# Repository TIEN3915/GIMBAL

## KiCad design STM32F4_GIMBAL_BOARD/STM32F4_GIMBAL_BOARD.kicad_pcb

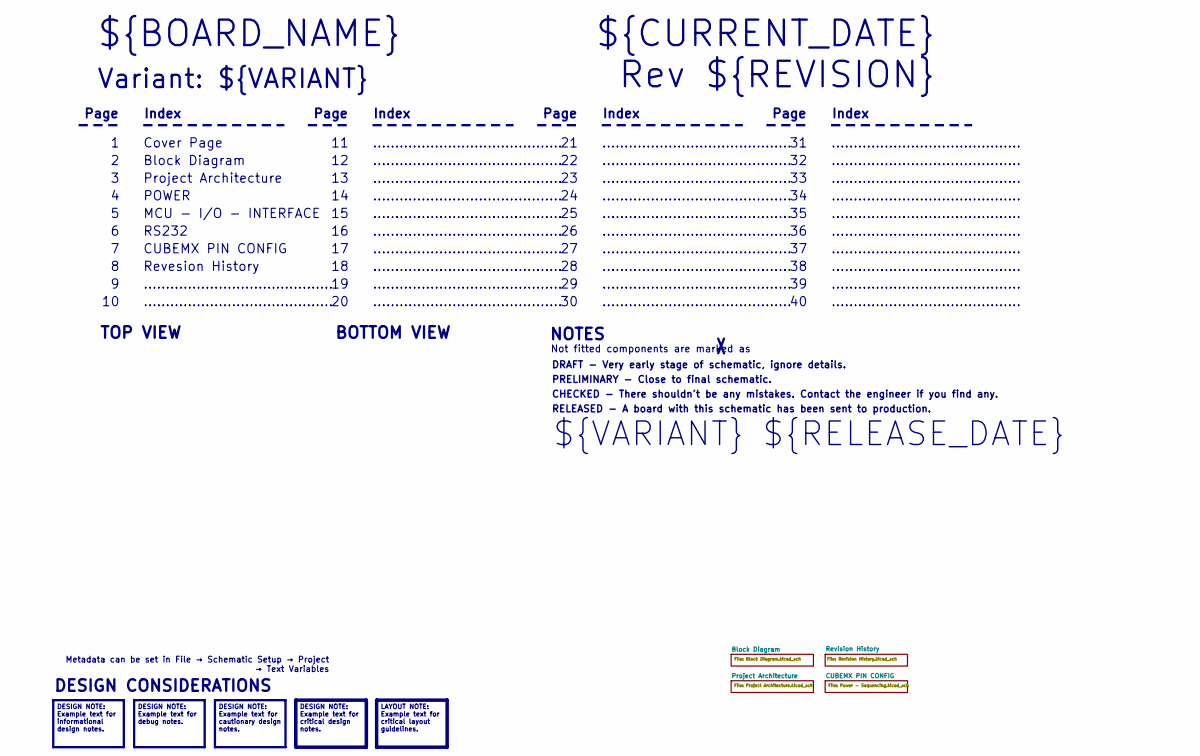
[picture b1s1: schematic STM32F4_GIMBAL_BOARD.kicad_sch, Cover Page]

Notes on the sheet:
Metadata can be set in File → Schematic Setup → Project → Text Variables
DESIGN NOTE: Example text for informational design notes.
LAYOUT NOTE: Example text for critical layout guidelines.
DESIGN NOTE: Example text for cautionary design notes.
DESIGN NOTE: Example text for debug notes.
DESIGN NOTE: Example text for critical design notes.
BOTTOM VIEW
...........................................
RELEASED - A board with this schematic has been sent to production.
Page
TOP VIEW
Revesion History
Not fitted components are marked as
Index
PRELIMINARY - Close to final schematic.
${VARIANT} ${RELEASE_DATE}
POWER
${CURRENT_DATE}
Variant: ${VARIANT}
Rev ${REVISION}
MCU - I/O - INTERFACE
${BOARD_NAME}
DRAFT - Very early stage of schematic, ignore details.
RS232
Block Diagram
Cover Page
NOTES
Project Architecture
CHECKED - There shouldn't be any mistakes. Contact the engineer if you find any.
DESIGN CONSIDERATIONS
CUBEMX PIN CONFIG

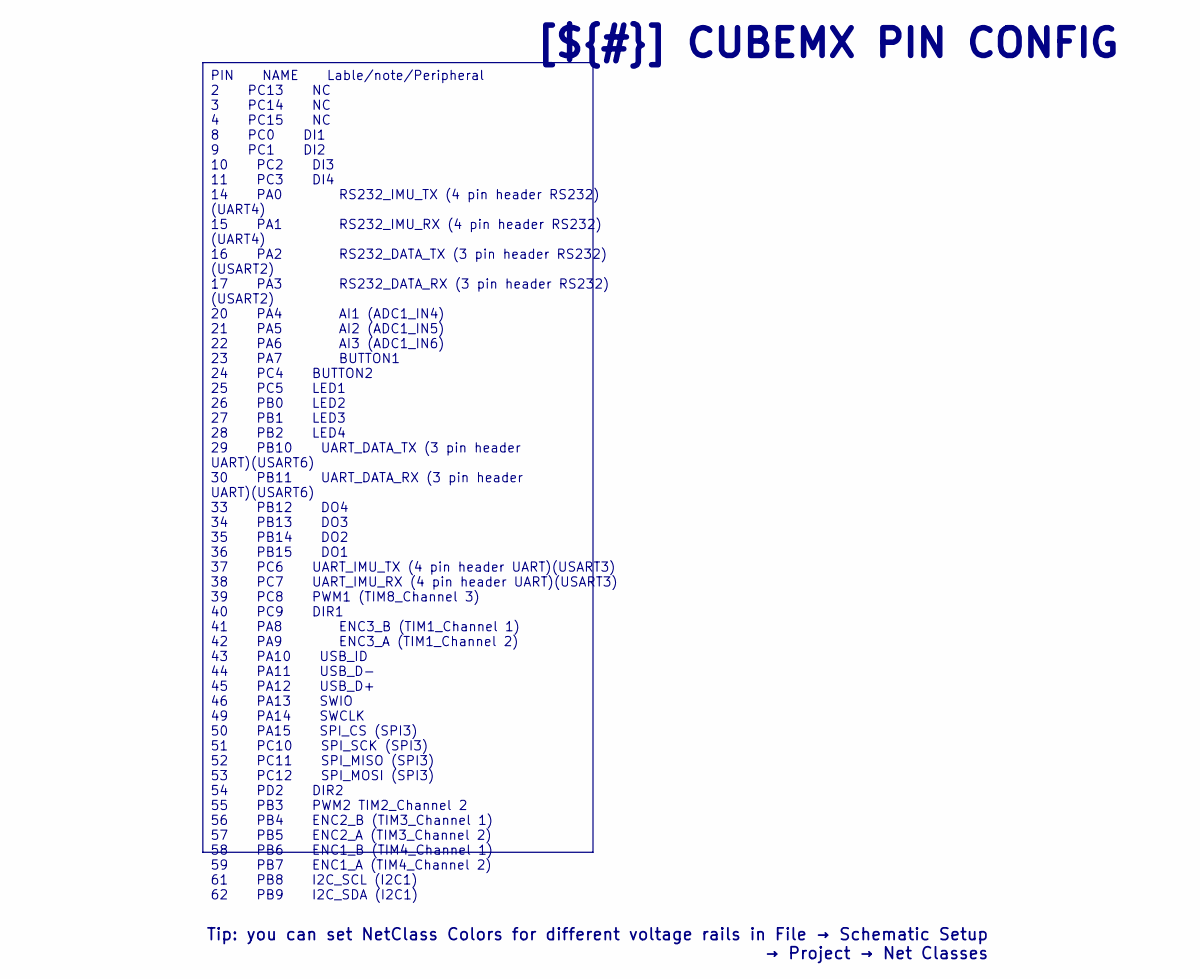
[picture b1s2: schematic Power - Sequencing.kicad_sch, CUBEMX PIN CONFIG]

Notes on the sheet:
PIN NAME Lable/note/Peripheral 2 PC13 NC 3 PC14 NC 4 PC15 NC 8 PC0 DI1 9 PC1 DI2 10 PC2 DI3 11 PC3 DI4 14 PA0 RS232_IMU_TX (4 pin header RS232) (UART4) 15 PA1 RS232_IMU_RX (4 pin header RS232) (UART4) 16 PA2 RS232_DATA_TX (3 pin header RS232) (USART2) 17 PA3 RS232_DATA_RX (3 pin header RS232) (USAR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
[${#}] ${TITLE}
Tip: you can set NetClass Colors for different voltage rails in File → Schematic Setup → Project → Net Classes

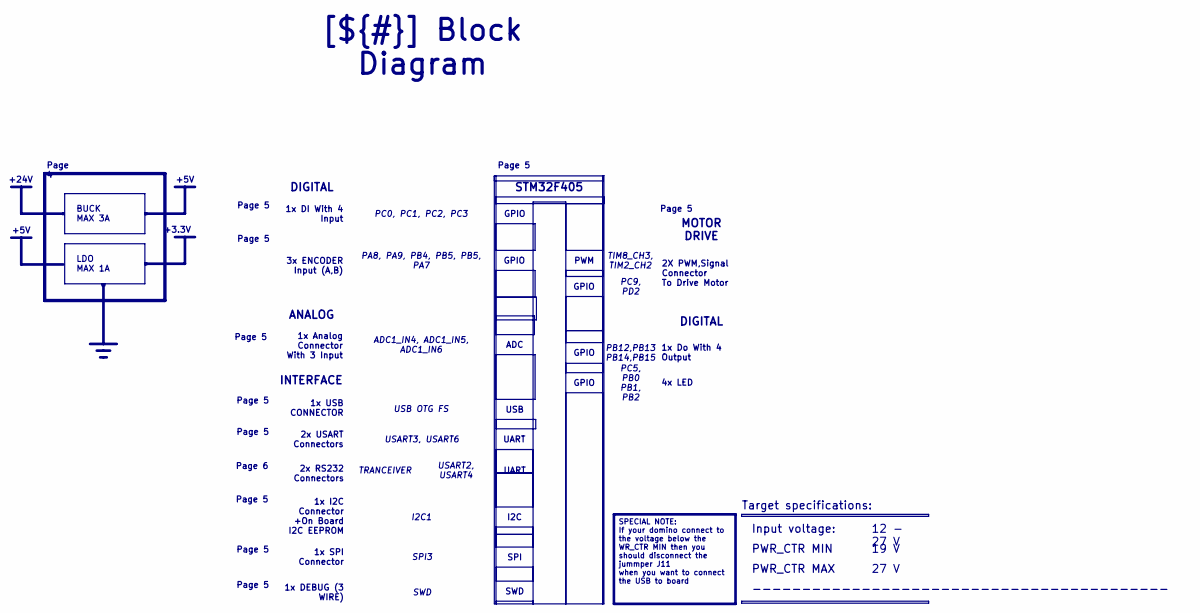
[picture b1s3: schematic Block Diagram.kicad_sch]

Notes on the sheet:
PWR_CTR MAX
LDO MAX 1A
GPIO
TRANCEIVER
GPIO
Page 6
PWR_CTR MIN
PA8, PA9, PB4, PB5, PB5, PA7
STM32F405
USART3, USART6
PC5, PB0 PB1, PB2
1x I2C Connector +On Board I2C EEPROM
Page 5
TIM8_CH3, TIM2_CH2
2x USART Connectors
Input voltage:
PC0, PC1, PC2, PC3
UART
19 V
SWD
PC9, PD2
1x Analog Connector With 3 Input
ADC1_IN4, ADC1_IN5, ADC1_IN6
MOTOR DRIVE
1x DEBUG (3 WIRE)
SPI
1x DI With 4 Input
SWD
1x SPI Connector
4x LED
USART2, USART4
2X PWM,Signal Connector To Drive Motor
Page 5
[${#}] ${TITLE}
Page 4
Target specifications:
SPI3
2x RS232 Connectors
27 V
ADC

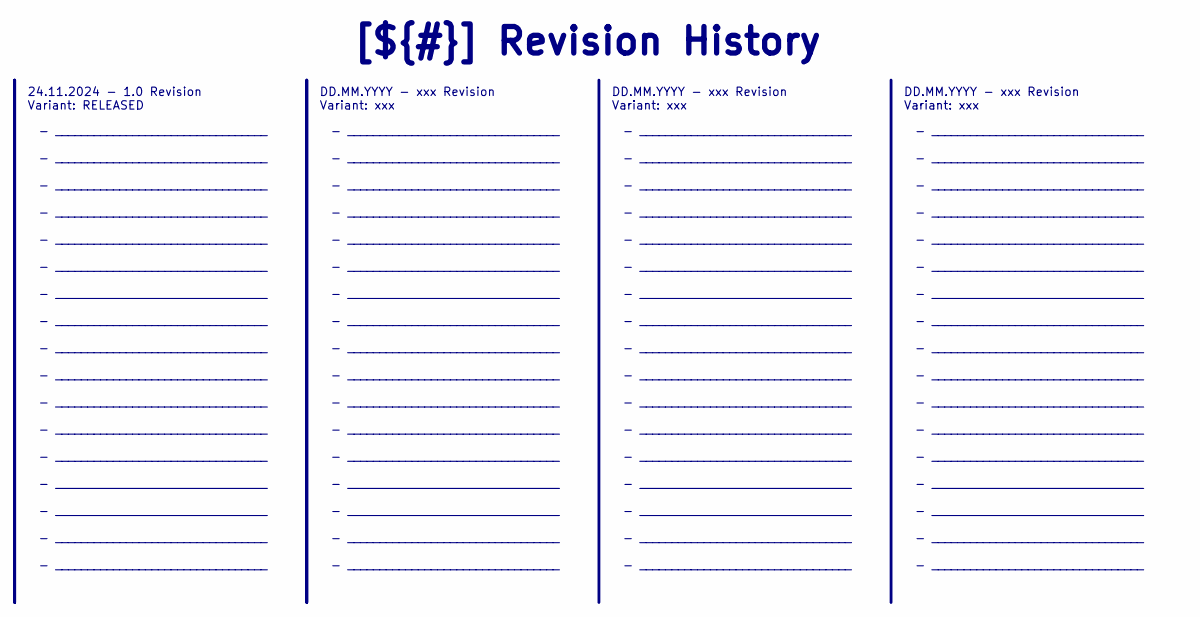
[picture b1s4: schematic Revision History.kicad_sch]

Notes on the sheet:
- _________________________________ - _________________________________ - _________________________________ - _________________________________ - _________________________________ - _________________________________ - _________________________________ - _________________________________ - _________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
DD.MM.YYYY - xxx Revision Variant: xxx
[${#}] ${TITLE}
24.11.2024 - 1.0 Revision Variant: RELEASED

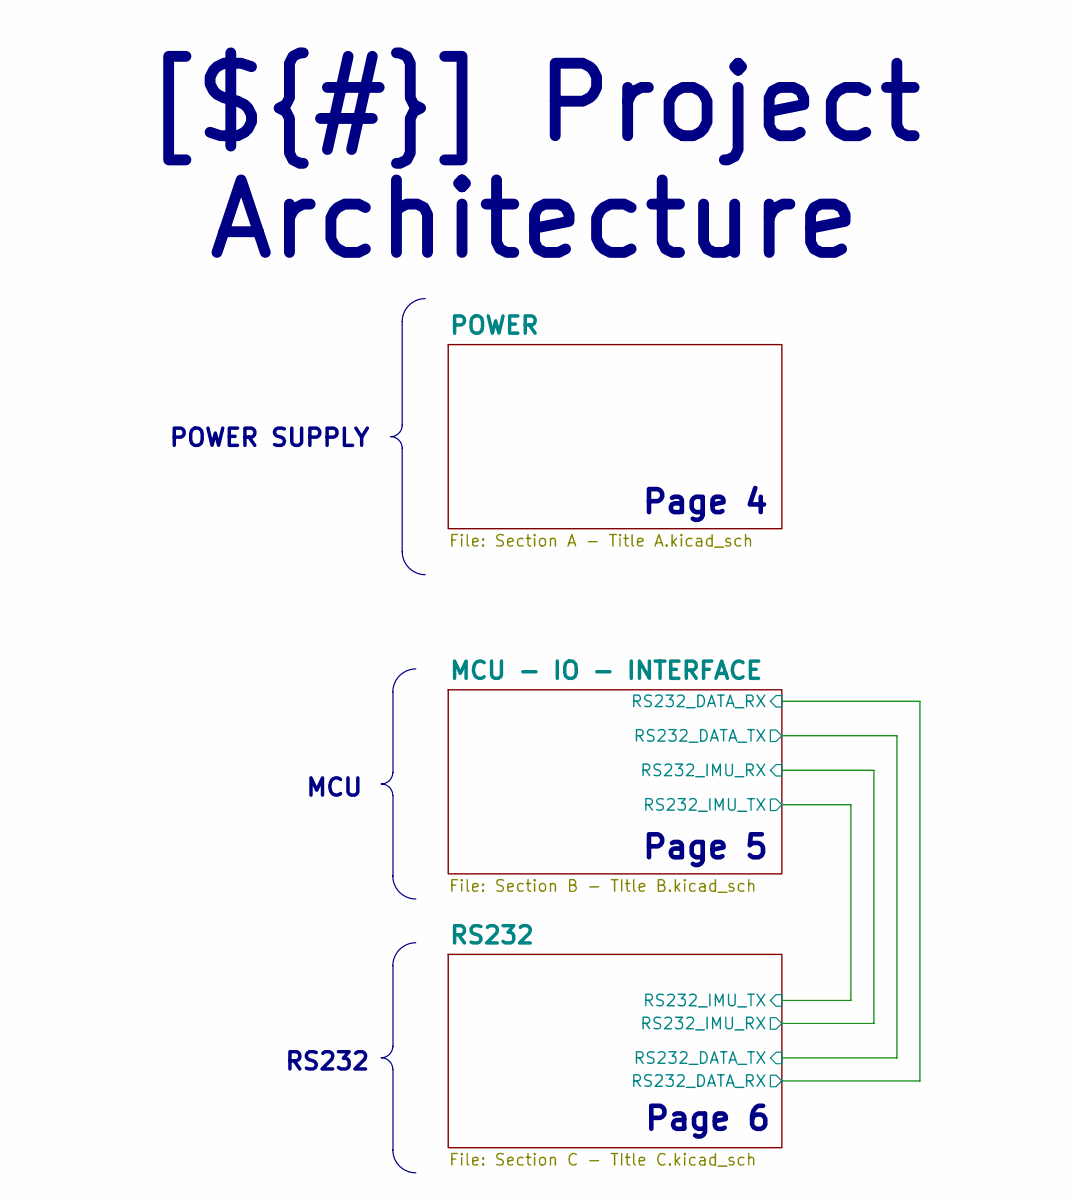
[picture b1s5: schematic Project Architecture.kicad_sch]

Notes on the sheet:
RS232
POWER SUPPLY
[${#}] ${TITLE}
MCU
Page 4
Page 6
Page 5

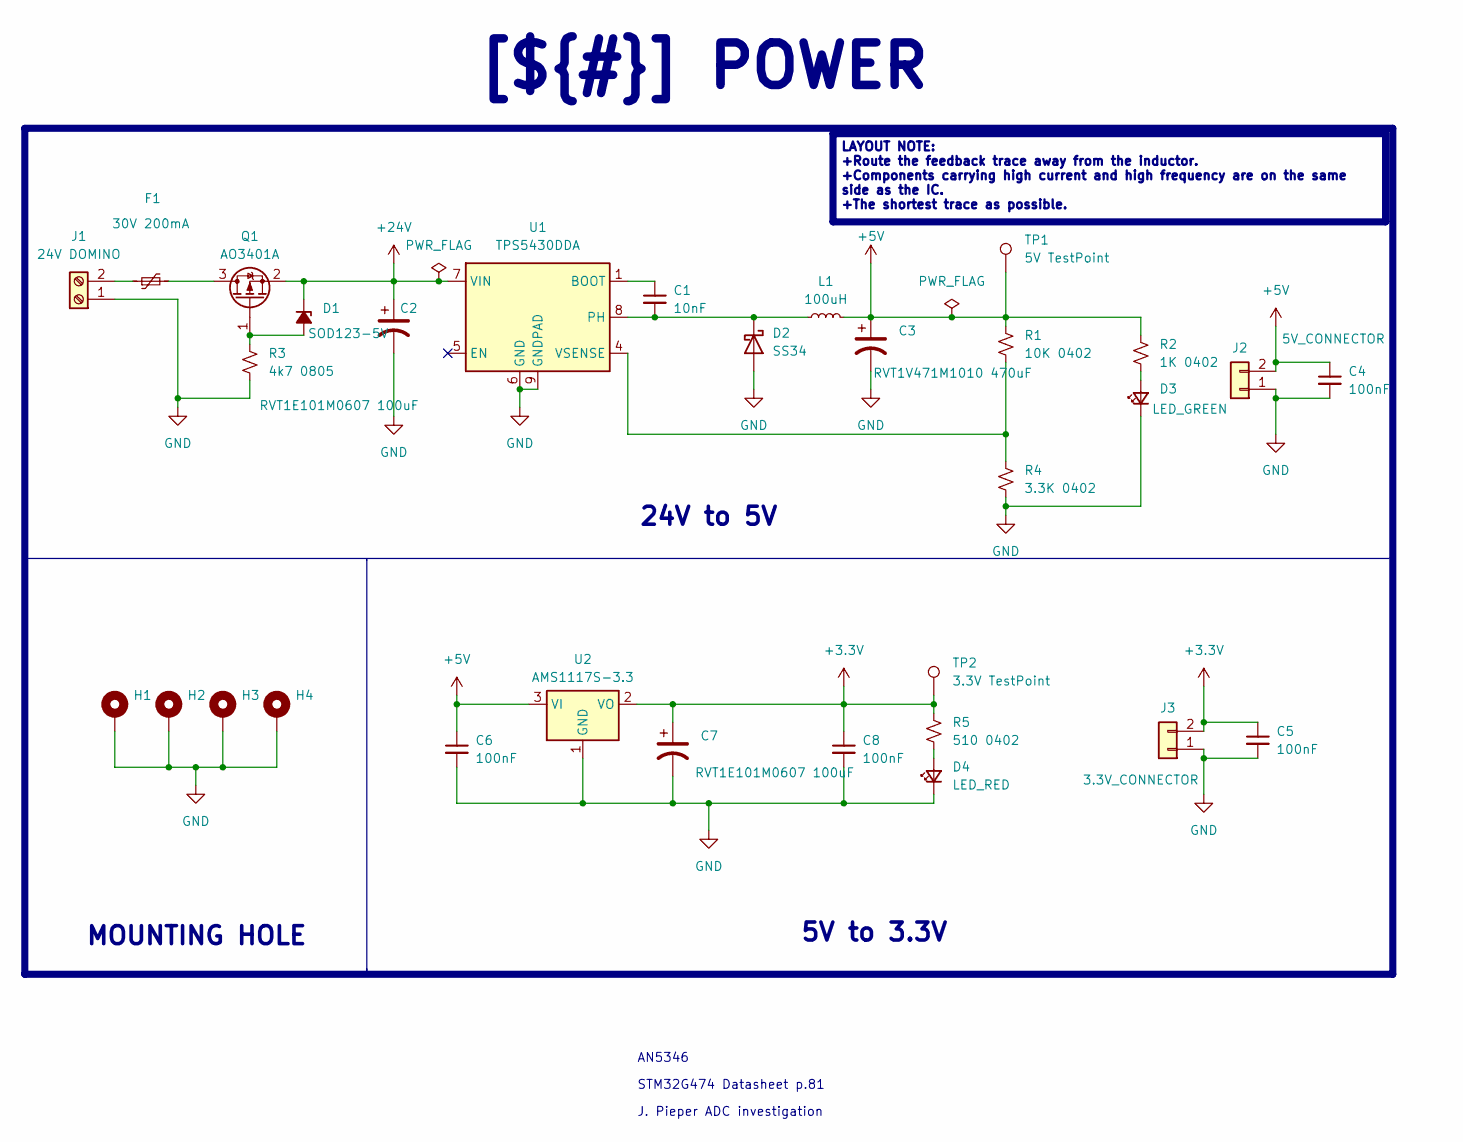
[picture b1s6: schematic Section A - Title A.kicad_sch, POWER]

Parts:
C1: 10nF; C_0402_1005Metric
C2, C7: RVT1E101M0607 100uF; CP_Elec_6.3x7.7
C3: RVT1V471M1010 470uF; CP_Elec_10x10.5
C4, C5, C6, C8: 100nF; C_0402_1005Metric
D1: SOD123-5V; D_SOD-123
D2: SS34; D_SMA
D3: LED_GREEN; LED_0603_1608Metric
D4: LED_RED; LED_0603_1608Metric
F1: 30V 200mA; Fuse_1812_4532Metric
H1, H2, H3, H4: MountingHole_Pad; MountingHole_2.7mm_M2.5_Pad_Via
J1: 24V DOMINO; KF142R5082P
J2: 5V_CONNECTOR; PinHeader_1x02_P2.54mm_Vertical
J3: 3.3V_CONNECTOR; PinHeader_1x02_P2.54mm_Vertical
L1: 100uH; L_12x12mm_H8mm
Q1: AO3401A; SOT-23
R1: 10K 0402; R_0402_1005Metric
R2: 1K 0402; R_0402_1005Metric
R3: 4k7 0805; R_0805_2012Metric
R4: 3.3K 0402; R_0402_1005Metric
R5: 510 0402; R_0402_1005Metric
TP1: 5V TestPoint; TestPoint_Pad_2.0x2.0mm
TP2: 3.3V TestPoint; TestPoint_Pad_2.0x2.0mm
U1: TPS5430DDA; TI_SO-PowerPAD-8_ThermalVias
U2: AMS1117S-3.3; SOT-223-3_TabPin2

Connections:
+3.3V: C5.1, C7.1, C8.1, J3.2, R5.1, TP2.1, U2.2 (VO); also elsewhere on the board
+5V: C3.1, C4.1, C6.1, J2.2, L1.2, R1.1, R2.1, TP1.1, U2.3 (VI); also elsewhere on the board
+24V: C2.1, D1.1 (K), Q1.2 (S), U1.7 (VIN); also elsewhere on the board
GND: C2.2, C3.2, C4.2, C5.2, C6.2, C7.2, C8.2, D2.2 (A), D3.1 (K), D4.1 (K), H1.1, H2.1, H3.1, H4.1, J1.1, J2.1, J3.1, R3.2, R4.2, U1.6 (GND), U1.9 (GNDPAD), U2.1 (GND); also elsewhere on the board
unnamed: D1.2 (A), Q1.1 (G), R3.1
unnamed: C1.2, D2.1 (K), L1.1, U1.8 (PH)
unnamed: D3.2 (A), R2.2
unnamed: D4.2 (A), R5.2
unnamed: F1.1, J1.2
unnamed: F1.2, Q1.3 (D)
unnamed: C1.1, U1.1 (BOOT)
unnamed: R1.2, R4.1, U1.4 (VSENSE)

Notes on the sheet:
MOUNTING HOLE
LAYOUT NOTE: +Route the feedback trace away from the inductor. +Components carrying high current and high frequency are on the same side as the IC. +The shortest trace as possible.
[${#}] ${TITLE}
5V to 3.3V
24V to 5V
J. Pieper ADC investigation
STM32G474 Datasheet p.81
AN5346

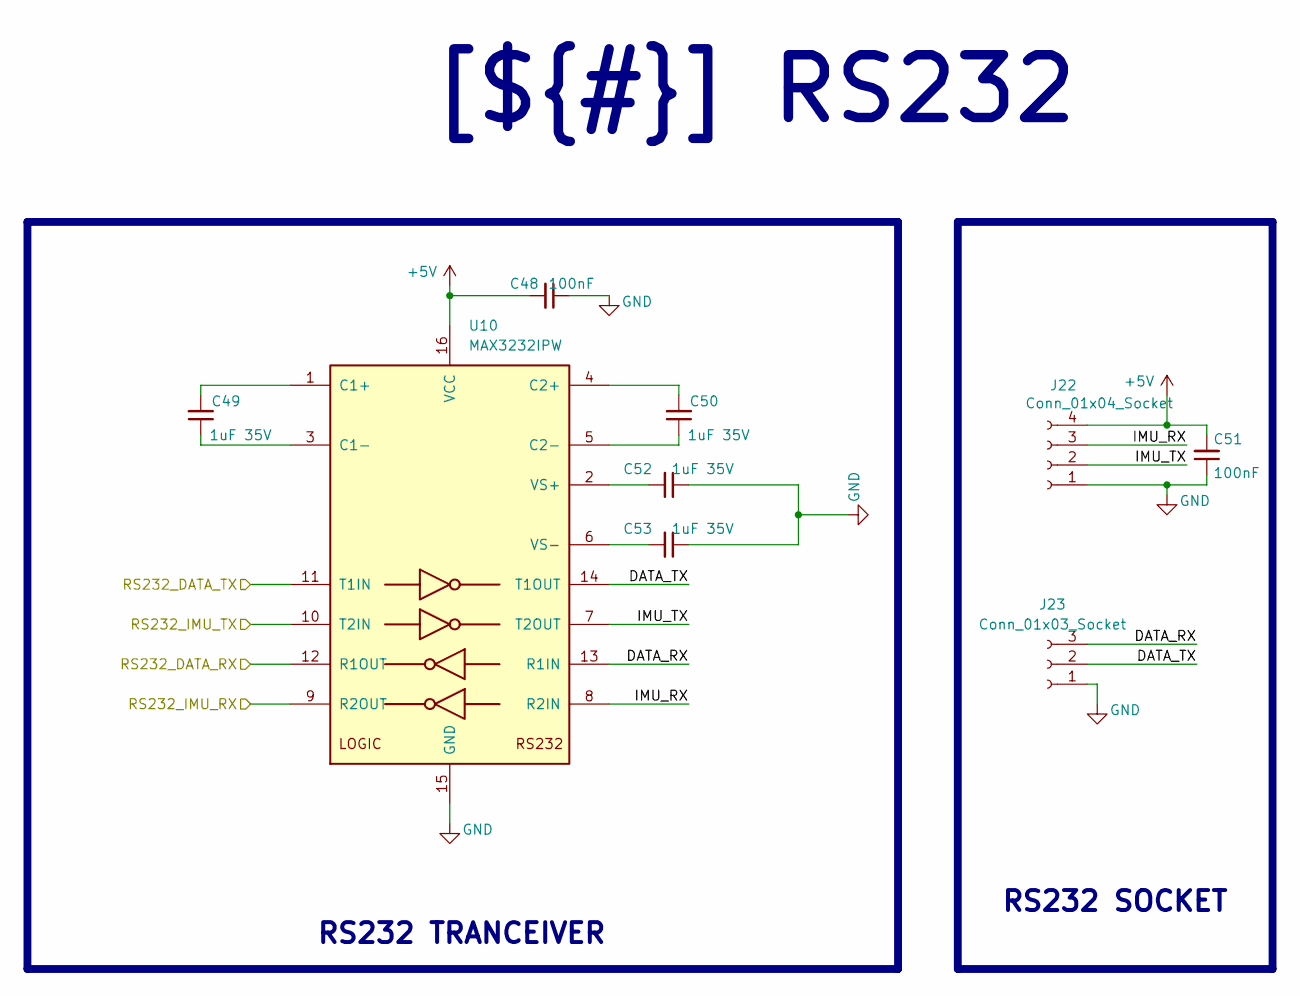
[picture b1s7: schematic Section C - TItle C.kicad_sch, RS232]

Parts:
C48, C51: 100nF; C_0402_1005Metric
C49, C50, C52, C53: 1uF 35V; C_0603_1608Metric
J22: Conn_01x04_Socket; JST_XH_B4B-XH-A_1x04_P2.50mm_Vertical
J23: Conn_01x03_Socket; JST_XH_B3B-XH-A_1x03_P2.50mm_Vertical
U10: MAX3232IPW; TSSOP-16_4.4x5mm_P0.65mm

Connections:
+5V: C48.2, C51.2, J22.4, U10.16 (VCC); also elsewhere on the board
/Project Architecture/MCU - IO - INTERFACE/RS232_DATA_RX: U10.12 (R1OUT); also elsewhere on the board
/Project Architecture/MCU - IO - INTERFACE/RS232_DATA_TX: U10.11 (T1IN); also elsewhere on the board
/Project Architecture/MCU - IO - INTERFACE/RS232_IMU_RX: U10.9 (R2OUT); also elsewhere on the board
/Project Architecture/MCU - IO - INTERFACE/RS232_IMU_TX: U10.10 (T2IN); also elsewhere on the board
/Project Architecture/RS232/DATA_RX: J23.3, U10.13 (R1IN)
/Project Architecture/RS232/DATA_TX: J23.2, U10.14 (T1OUT)
/Project Architecture/RS232/IMU_RX: J22.3, U10.8 (R2IN)
/Project Architecture/RS232/IMU_TX: J22.2, U10.7 (T2OUT)
GND: C48.1, C51.1, C52.1, C53.1, J22.1, J23.1, U10.15 (GND); also elsewhere on the board
unnamed: C49.2, U10.1 (C1+)
unnamed: C49.1, U10.3 (C1-)
unnamed: C50.2, U10.4 (C2+)
unnamed: C50.1, U10.5 (C2-)
unnamed: C52.2, U10.2 (VS+)
unnamed: C53.2, U10.6 (VS-)

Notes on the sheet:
RS232 TRANCEIVER
RS232 SOCKET
[${#}] ${TITLE}

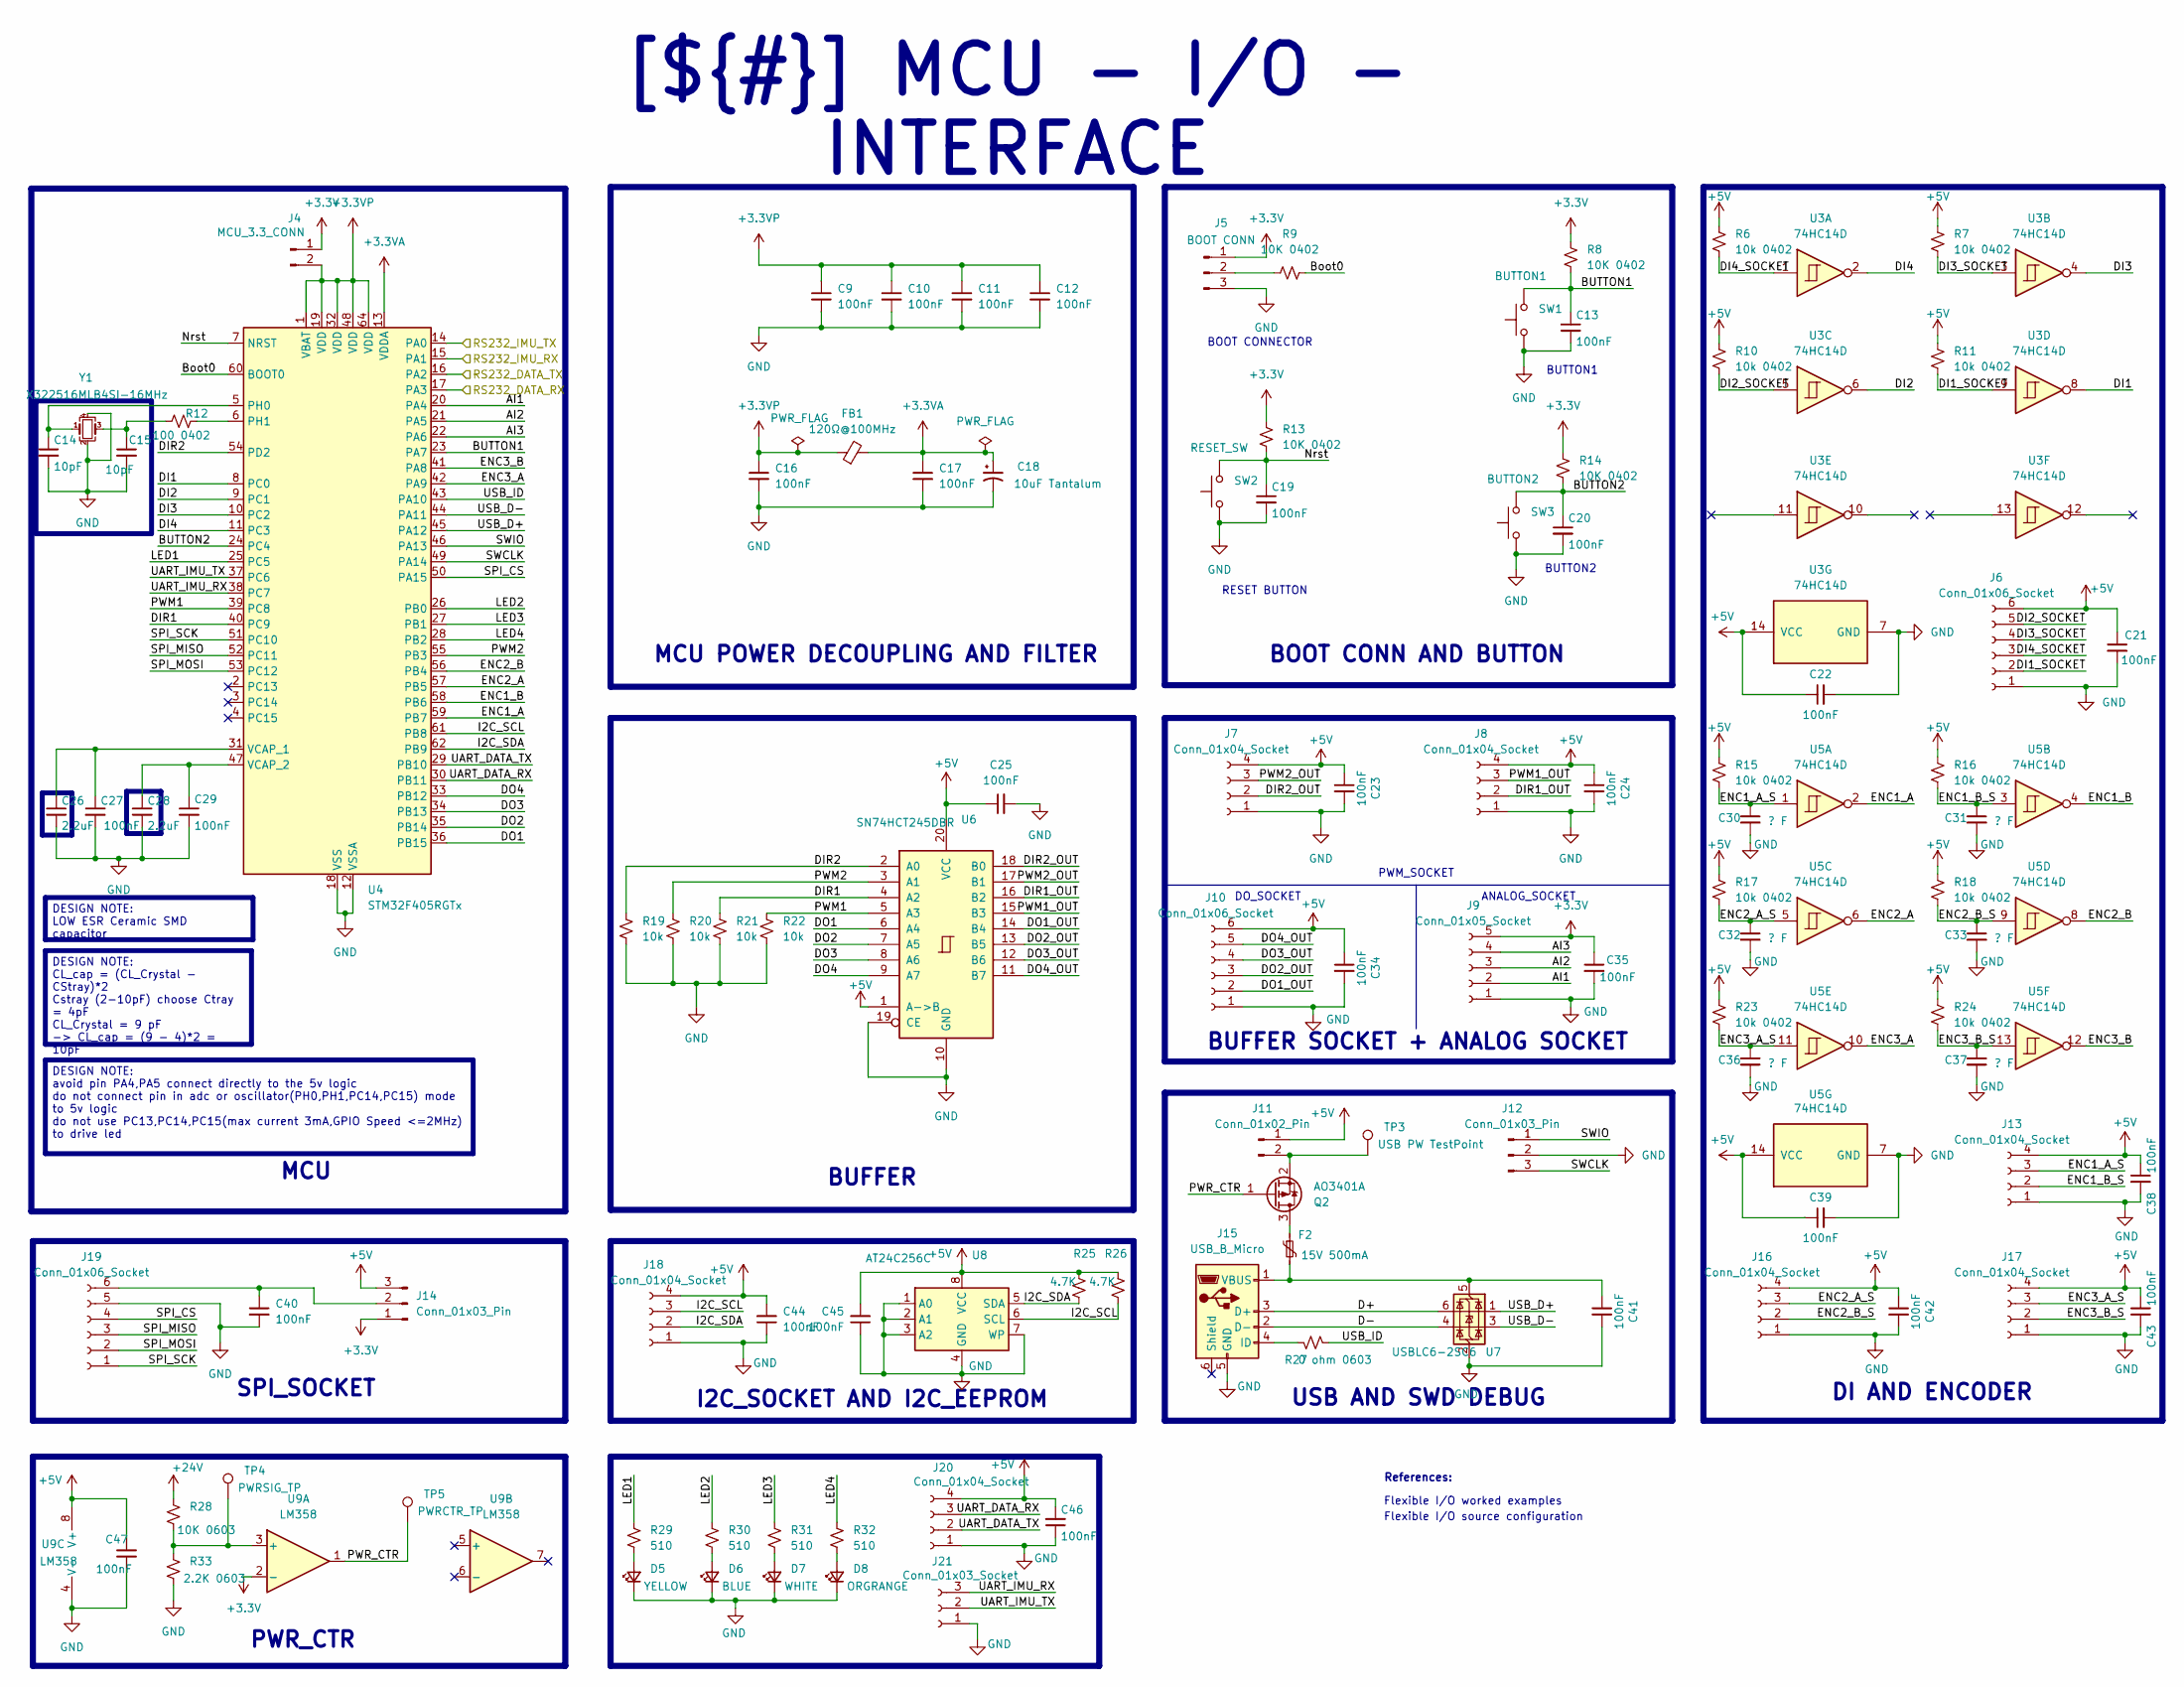
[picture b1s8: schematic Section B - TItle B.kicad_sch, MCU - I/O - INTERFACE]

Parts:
C9, C10, C11, C12, C13, C16, C17, C19, C20, C21, C22, C23, C24, C25, C27, C29, C34, C35, C38, C39, C40, C41, C42, C43, C44, C45, C46, C47: 100nF; C_0402_1005Metric
C14, C15: 10pF; C_0402_1005Metric
C18: 10uF Tantalum; CP_EIA-3216-18_Kemet-A_Pad1.58x1.35mm_HandSolder
C26, C28: 2.2uF; C_0402_1005Metric
C30, C31, C32, C33, C36, C37: ? F; C_0603_1608Metric
D5: YELLOW; LED_0603_1608Metric
D6: BLUE; LED_0603_1608Metric
D7: WHITE; LED_0603_1608Metric
D8: ORGRANGE; LED_0603_1608Metric
F2: 15V 500mA; Fuse_1812_4532Metric
FB1: 120Ω@100MHz; L_0603_1608Metric
J4: MCU_3.3_CONN; PinHeader_1x02_P2.54mm_Vertical
J5: BOOT CONN; PinHeader_1x03_P2.54mm_Vertical
J6, J10, J19: Conn_01x06_Socket; JST_XH_B6B-XH-A_1x06_P2.50mm_Vertical
J7, J8, J13, J16, J17, J18, J20: Conn_01x04_Socket; JST_XH_B4B-XH-A_1x04_P2.50mm_Vertical
J9: Conn_01x05_Socket; JST_XH_B5B-XH-A_1x05_P2.50mm_Vertical
J11: Conn_01x02_Pin; PinHeader_1x02_P2.54mm_Vertical
J12, J14: Conn_01x03_Pin; PinHeader_1x03_P2.54mm_Vertical
J15: USB_B_Micro; USB_Micro-B_Wuerth_629105150521
J21: Conn_01x03_Socket; JST_XH_B3B-XH-A_1x03_P2.50mm_Vertical
Q2: AO3401A; SOT-23
R6, R7, R10, R11, R15, R16, R17, R18, R23, R24: 10k 0402; R_0402_1005Metric
R8, R9, R13, R14: 10K 0402; R_0402_1005Metric
R12: 100 0402; R_0402_1005Metric
R19, R20, R21, R22: 10k; R_0402_1005Metric
R25, R26: 4.7K; R_0402_1005Metric
R27: 0 ohm 0603; R_0603_1608Metric_Pad0.98x0.95mm_HandSolder
R28: 10K 0603; R_0603_1608Metric
R29, R30, R31, R32: 510; R_0402_1005Metric
R33: 2.2K 0603; R_0603_1608Metric
SW1: BUTTON1; SW_PUSH_6mm
SW2: RESET_SW; SW_PUSH_6mm
SW3: BUTTON2; SW_PUSH_6mm
TP3: USB PW TestPoint; TestPoint_Pad_2.0x2.0mm
TP4: PWRSIG_TP; TestPoint_Pad_2.0x2.0mm
TP5: PWRCTR_TP; TestPoint_Pad_2.0x2.0mm
U3, U5: 74HC14D; SOIC-14_3.9x8.7mm_P1.27mm
U4: STM32F405RGTx; LQFP-64_10x10mm_P0.5mm
U6: SN74HCT245DBR; SSOP-20_5.3x7.2mm_P0.65mm
U7: USBLC6-2SC6; SOT-23-6
U8: AT24C256C; SOIC-8_3.9x4.9mm_P1.27mm
U9: LM358; SOIC-8_3.9x4.9mm_P1.27mm
Y1: X322516MLB4SI-16MHz; Crystal_SMD_3225-4Pin_3.2x2.5mm

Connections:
+3.3V: C35.1, J4.1, J5.1, J9.5, J14.1, R8.1, R13.1, R14.1, U9.2 (-); also elsewhere on the board
+3.3VA: C17.1, C18.1, FB1.2, U4.13 (VDDA)
+3.3VP: C9.1, C10.1, C11.1, C12.1, C16.1, FB1.1, J4.2, U4.1 (VBAT), U4.19 (VDD), U4.32 (VDD), U4.48 (VDD), U4.64 (VDD)
+5V: C21.1, C22.1, C23.1, C24.1, C25.1, C34.1, C38.1, C39.1, C42.1, C43.1, C44.2, C45.2, C46.2, C47.1, J6.6, J7.4, J8.4, J10.6, J11.1, J13.4, J14.3, J16.4, J17.4, J18.4, J20.4, R6.1, R7.1, R10.1, R11.1, R15.1, R16.1, R17.1, R18.1, R23.1, R24.1, R25.1, R26.1, U3.14 (VCC), U5.14 (VCC), U6.1 (A->B), U6.20 (VCC), U8.8 (VCC), U9.8 (V+); also elsewhere on the board
+24V: R28.1; also elsewhere on the board
/Project Architecture/MCU - IO - INTERFACE/AI1: J9.2, U4.20 (PA4)
/Project Architecture/MCU - IO - INTERFACE/AI2: J9.3, U4.21 (PA5)
/Project Architecture/MCU - IO - INTERFACE/AI3: J9.4, U4.22 (PA6)
/Project Architecture/MCU - IO - INTERFACE/BUTTON1: C13.1, R8.2, SW1.2, U4.23 (PA7)
/Project Architecture/MCU - IO - INTERFACE/BUTTON2: C20.1, R14.2, SW3.2, U4.24 (PC4)
/Project Architecture/MCU - IO - INTERFACE/Boot0: R9.2, U4.60 (BOOT0)
/Project Architecture/MCU - IO - INTERFACE/D+: J15.3 (D+), U7.6 (I/O1)
/Project Architecture/MCU - IO - INTERFACE/D-: J15.2 (D-), U7.4 (I/O2)
/Project Architecture/MCU - IO - INTERFACE/DI1: U3.8, U4.8 (PC0)
/Project Architecture/MCU - IO - INTERFACE/DI1_SOCKET: J6.2, R11.2, U3.9
/Project Architecture/MCU - IO - INTERFACE/DI2: U3.6, U4.9 (PC1)
/Project Architecture/MCU - IO - INTERFACE/DI2_SOCKET: J6.5, R10.2, U3.5
/Project Architecture/MCU - IO - INTERFACE/DI3: U3.4, U4.10 (PC2)
/Project Architecture/MCU - IO - INTERFACE/DI3_SOCKET: J6.4, R7.2, U3.3
/Project Architecture/MCU - IO - INTERFACE/DI4: U3.2, U4.11 (PC3)
/Project Architecture/MCU - IO - INTERFACE/DI4_SOCKET: J6.3, R6.2, U3.1
/Project Architecture/MCU - IO - INTERFACE/DIR1: R21.1, U4.40 (PC9), U6.4 (A2)
/Project Architecture/MCU - IO - INTERFACE/DIR1_OUT: J8.2, U6.16 (B2)
/Project Architecture/MCU - IO - INTERFACE/DIR2: R19.1, U4.54 (PD2), U6.2 (A0)
/Project Architecture/MCU - IO - INTERFACE/DIR2_OUT: J7.2, U6.18 (B0)
/Project Architecture/MCU - IO - INTERFACE/DO1: U4.36 (PB15), U6.6 (A4)
/Project Architecture/MCU - IO - INTERFACE/DO1_OUT: J10.2, U6.14 (B4)
/Project Architecture/MCU - IO - INTERFACE/DO2: U4.35 (PB14), U6.7 (A5)
/Project Architecture/MCU - IO - INTERFACE/DO2_OUT: J10.3, U6.13 (B5)
/Project Architecture/MCU - IO - INTERFACE/DO3: U4.34 (PB13), U6.8 (A6)
/Project Architecture/MCU - IO - INTERFACE/DO3_OUT: J10.4, U6.12 (B6)
/Project Architecture/MCU - IO - INTERFACE/DO4: U4.33 (PB12), U6.9 (A7)
/Project Architecture/MCU - IO - INTERFACE/DO4_OUT: J10.5, U6.11 (B7)
/Project Architecture/MCU - IO - INTERFACE/ENC1_A: U4.59 (PB7), U5.2
/Project Architecture/MCU - IO - INTERFACE/ENC1_A_S: C30.1, J13.3, R15.2, U5.1
/Project Architecture/MCU - IO - INTERFACE/ENC1_B: U4.58 (PB6), U5.4
/Project Architecture/MCU - IO - INTERFACE/ENC1_B_S: C31.1, J13.2, R16.2, U5.3
/Project Architecture/MCU - IO - INTERFACE/ENC2_A: U4.57 (PB5), U5.6
/Project Architecture/MCU - IO - INTERFACE/ENC2_A_S: C32.1, J16.3, R17.2, U5.5
/Project Architecture/MCU - IO - INTERFACE/ENC2_B: U4.56 (PB4), U5.8
/Project Architecture/MCU - IO - INTERFACE/ENC2_B_S: C33.1, J16.2, R18.2, U5.9
/Project Architecture/MCU - IO - INTERFACE/ENC3_A: U4.42 (PA9), U5.10
/Project Architecture/MCU - IO - INTERFACE/ENC3_A_S: C36.1, J17.3, R23.2, U5.11
/Project Architecture/MCU - IO - INTERFACE/ENC3_B: U4.41 (PA8), U5.12
/Project Architecture/MCU - IO - INTERFACE/ENC3_B_S: C37.1, J17.2, R24.2, U5.13
/Project Architecture/MCU - IO - INTERFACE/I2C_SCL: J18.3, R26.2, U4.61 (PB8), U8.6 (SCL)
/Project Architecture/MCU - IO - INTERFACE/I2C_SDA: J18.2, R25.2, U4.62 (PB9), U8.5 (SDA)
/Project Architecture/MCU - IO - INTERFACE/LED1: R29.1, U4.25 (PC5)
/Project Architecture/MCU - IO - INTERFACE/LED2: R30.1, U4.26 (PB0)
/Project Architecture/MCU - IO - INTERFACE/LED3: R31.1, U4.27 (PB1)
/Project Architecture/MCU - IO - INTERFACE/LED4: R32.1, U4.28 (PB2)
/Project Architecture/MCU - IO - INTERFACE/Nrst: C19.1, R13.2, SW2.2, U4.7 (NRST)
/Project Architecture/MCU - IO - INTERFACE/PWM1: R22.1, U4.39 (PC8), U6.5 (A3)
/Project Architecture/MCU - IO - INTERFACE/PWM1_OUT: J8.3, U6.15 (B3)
/Project Architecture/MCU - IO - INTERFACE/PWM2: R20.1, U4.55 (PB3), U6.3 (A1)
/Project Architecture/MCU - IO - INTERFACE/PWM2_OUT: J7.3, U6.17 (B1)
/Project Architecture/MCU - IO - INTERFACE/PWR_CTR: Q2.1 (G), TP5.1, U9.1
/Project Architecture/MCU - IO - INTERFACE/RS232_DATA_RX: U4.17 (PA3); also elsewhere on the board
/Project Architecture/MCU - IO - INTERFACE/RS232_DATA_TX: U4.16 (PA2); also elsewhere on the board
/Project Architecture/MCU - IO - INTERFACE/RS232_IMU_RX: U4.15 (PA1); also elsewhere on the board
/Project Architecture/MCU - IO - INTERFACE/RS232_IMU_TX: U4.14 (PA0); also elsewhere on the board
/Project Architecture/MCU - IO - INTERFACE/SPI_CS: J19.4, U4.50 (PA15)
/Project Architecture/MCU - IO - INTERFACE/SPI_MISO: J19.3, U4.52 (PC11)
/Project Architecture/MCU - IO - INTERFACE/SPI_MOSI: J19.2, U4.53 (PC12)
/Project Architecture/MCU - IO - INTERFACE/SPI_SCK: J19.1, U4.51 (PC10)
/Project Architecture/MCU - IO - INTERFACE/SWCLK: J12.3, U4.49 (PA14)
/Project Architecture/MCU - IO - INTERFACE/SWIO: J12.1, U4.46 (PA13)
/Project Architecture/MCU - IO - INTERFACE/UART_DATA_RX: J20.3, U4.30 (PB11)
/Project Architecture/MCU - IO - INTERFACE/UART_DATA_TX: J20.2, U4.29 (PB10)
/Project Architecture/MCU - IO - INTERFACE/UART_IMU_RX: J21.3, U4.38 (PC7)
/Project Architecture/MCU - IO - INTERFACE/UART_IMU_TX: J21.2, U4.37 (PC6)
/Project Architecture/MCU - IO - INTERFACE/USB_D+: U4.45 (PA12), U7.1 (I/O1)
/Project Architecture/MCU - IO - INTERFACE/USB_D-: U4.44 (PA11), U7.3 (I/O2)
/Project Architecture/MCU - IO - INTERFACE/USB_ID: R27.2, U4.43 (PA10)
GND: C9.2, C10.2, C11.2, C12.2, C13.2, C14.2, C15.2, C16.2, C17.2, C18.2, C19.2, C20.2, C21.2, C22.2, C23.2, C24.2, C25.2, C26.2, C27.2, C28.2, C29.2, C30.2, C31.2, C32.2, C33.2, C34.2, C35.2, C36.2, C37.2, C38.2, C39.2, C40.2, C41.2, C42.2, C43.2, C44.1, C45.1, C46.1, C47.2, D5.1 (K), D6.1 (K), D7.1 (K), D8.1 (K), J5.3, J6.1, J7.1, J8.1, J9.1, J10.1, J12.2, J13.1, J15.5 (GND), J16.1, J17.1, J18.1, J19.5, J20.1, J21.1, R19.2, R20.2, R21.2, R22.2, R33.2, SW1.1, SW2.1, SW3.1, U3.7 (GND), U4.12 (VSSA), U4.18 (VSS), U4.63 (VSS), U5.7 (GND), U6.10 (GND), U6.19 (CE), U7.2 (GND), U8.1 (A0), U8.2 (A1), U8.3 (A2), U8.4 (GND), U8.7 (WP), U9.4 (V-), Y1.2, Y1.4; also elsewhere on the board
unnamed: C15.1, R12.1, Y1.3
unnamed: D5.2 (A), R29.2
unnamed: D6.2 (A), R30.2
unnamed: D7.2 (A), R31.2
unnamed: D8.2 (A), R32.2
unnamed: J5.2, R9.1
unnamed: J11.2, Q2.2 (S), TP3.1
unnamed: C40.1, J14.2, J19.6
unnamed: J15.4 (ID), R27.1
unnamed: C41.1, F2.2, J15.1 (VBUS), U7.5 (VBUS)
unnamed: F2.1, Q2.3 (D)
unnamed: C14.1, U4.5 (PH0), Y1.1
unnamed: R12.2, U4.6 (PH1)
unnamed: C26.1, C27.1, U4.31 (VCAP_1)
unnamed: C28.1, C29.1, U4.47 (VCAP_2)
unnamed: R28.2, R33.1, TP4.1, U9.3 (+)

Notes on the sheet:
BOOT CONN AND BUTTON
I2C_SOCKET AND I2C_EEPROM
[${#}] ${TITLE}
SPI_SOCKET
DESIGN NOTE: CL_cap = (CL_Crystal - CStray)*2 Cstray (2-10pF) choose Ctray = 4pF CL_Crystal = 9 pF -> CL_cap = (9 - 4)*2 = 10pF
USB AND SWD DEBUG
MCU
MCU POWER DECOUPLING AND FILTER
BUFFER SOCKET + ANALOG SOCKET
PWR_CTR
DI AND ENCODER
DESIGN NOTE: LOW ESR Ceramic SMD capacitor
DESIGN NOTE: avoid pin PA4,PA5 connect directly to the 5v logic do not connect pin in adc or oscillator(PH0,PH1,PC14,PC15) mode to 5v logic do not use PC13,PC14,PC15(max current 3mA,GPIO Speed <=2MHz) to drive led
BUFFER
Flexible I/O worked examples
BOOT CONNECTOR
PWM_SOCKET
BUTTON2
ANALOG_SOCKET
RESET BUTTON
DO_SOCKET
References:
BUTTON1
Flexible I/O source configuration
